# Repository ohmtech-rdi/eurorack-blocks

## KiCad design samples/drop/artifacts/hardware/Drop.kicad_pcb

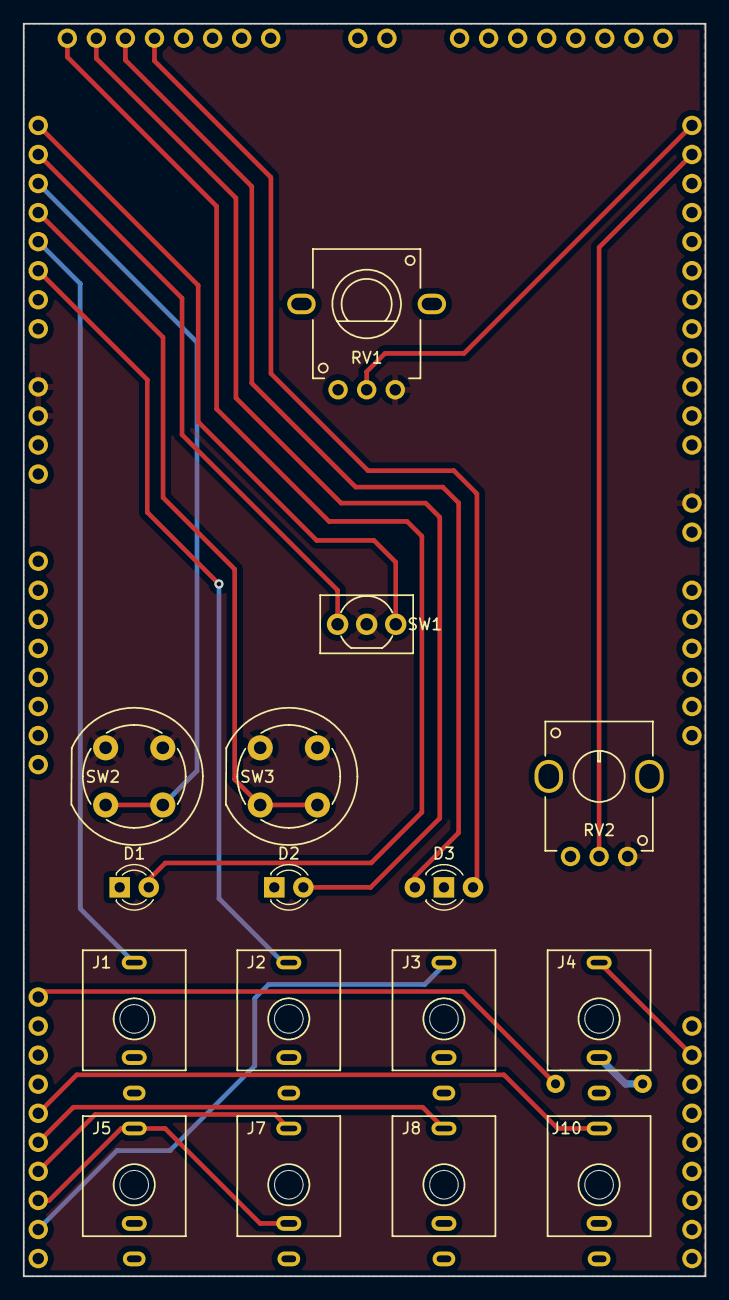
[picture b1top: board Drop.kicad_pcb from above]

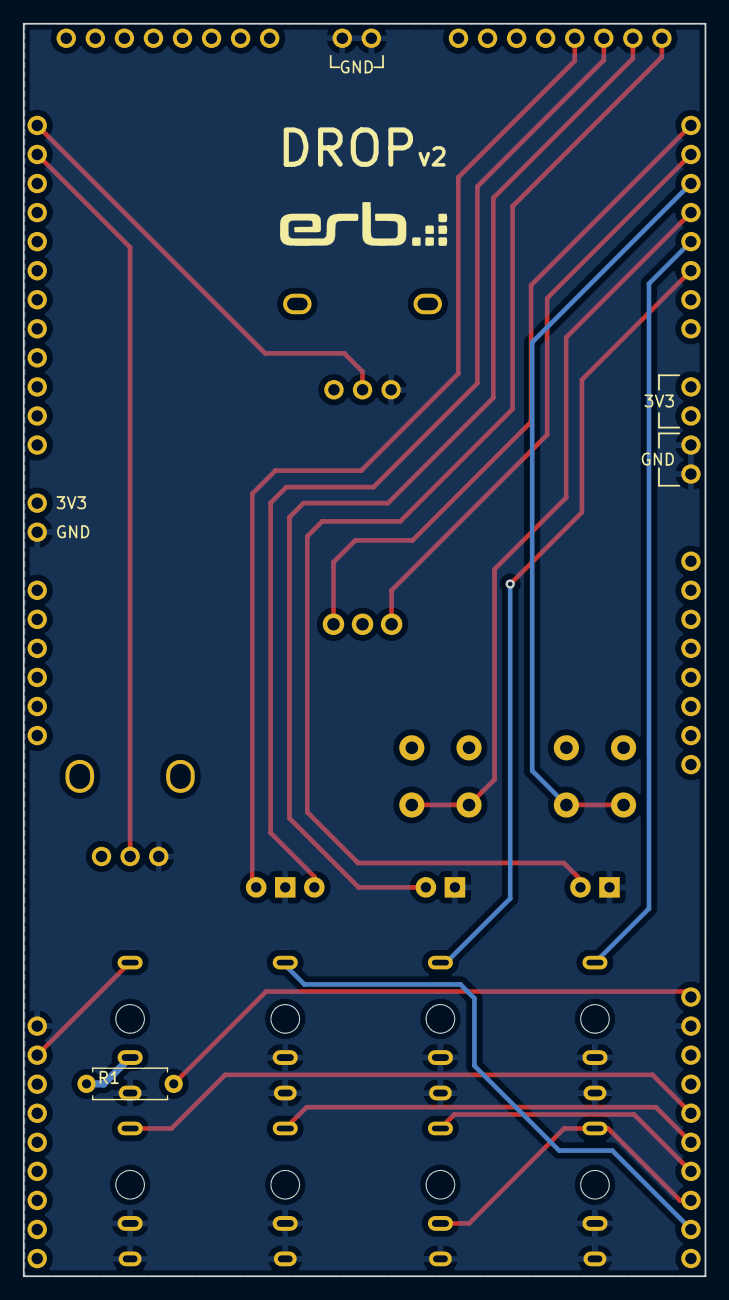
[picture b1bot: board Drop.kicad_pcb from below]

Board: 2 copper layers, 59.6 x 109.5 mm, 39 parts (12 on the bottom side), 22 nets.

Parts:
D1, D2: LED; LED_D3.0mm
D3: LED_Dual_ACA; LED_D3.0mm-3
H1: Header1; Empty
H2: Header2; Empty
H3: ROGAN 6PS; Empty
H4, H5, H6, H7, H8, H9, H10, H11: KNURLED NUT; Empty
J1, J2, J3, J4, J5, J7, J8, J10: IN; ThonkiconnJack
J6: POWER2; PinHeader_1x04_P2.54mm_Vertical
J9: POWER1; PinHeader_1x02_P2.54mm_Vertical
J11: GND; PinHeader_1x02_P2.54mm_Vertical
R1: 10k; R_Axial_DIN0207_L6.3mm_D2.5mm_P7.62mm_Horizontal
RV1: 100k; AlphaPot9ShaftD
RV2: 100k; SongHueiTallTrim9
SW1: SW_SPDT; SW_SPDT_Dailywell
SW2, SW3: SW_Push_Dual; SW_SPST_CKD6R
ZZ1: PX; PinHeader_1x12_P2.54mm_Vertical
ZZ2: CIX; PinHeader_1x09_P2.54mm_Vertical
ZZ3, ZZ7: BX; PinHeader_1x08_P2.54mm_Vertical
ZZ4, ZZ12: LX; PinHeader_1x08_P2.54mm_Vertical
ZZ5: ANALOG; PinHeader_1x10_P2.54mm_Vertical
ZZ10: SD; PinHeader_1x06_P2.54mm_Vertical

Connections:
+3V3: J6.1, J6.2, J9.1, RV1.3, RV2.3, SW1.2, SW2.1, SW3.1
AI1: J5.T, J7.TN, ZZ5.8
AI2: J7.T, ZZ5.7
AO1: J8.T, ZZ5.6
AO2: J10.T, ZZ5.5
B1: SW1.1, ZZ3.1
B2: SW1.3, ZZ3.2
B3: SW2.2, ZZ3.3
B4: SW3.2, ZZ3.4
B5: J1.T, ZZ3.5
B6: J2.T, ZZ3.6
CI1: J4.T, ZZ2.2
GND: D1.1, D2.1, D3.2, J1.S, J1.TN, J2.S, J2.TN, J3.S, J3.TN, J4.S, J5.S, J5.TN, J6.3, J6.4, J7.S, J8.S, J8.TN, J9.2, J10.S, J10.TN, J11.1, J11.2, RV1.1, RV2.1, ZZ2.1, ZZ5.2
GO1: J3.T, ZZ5.9
L1: D1.2, ZZ4.1
L2: D2.2, ZZ4.2
L3: D3.1, ZZ4.3
L4: D3.3, ZZ4.4
NPR0: R1.1, ZZ5.1
P1: RV1.2, ZZ1.1
P2: RV2.2, ZZ1.2
freq_cv-Net-(J1-PadTN): J4.TN, R1.2

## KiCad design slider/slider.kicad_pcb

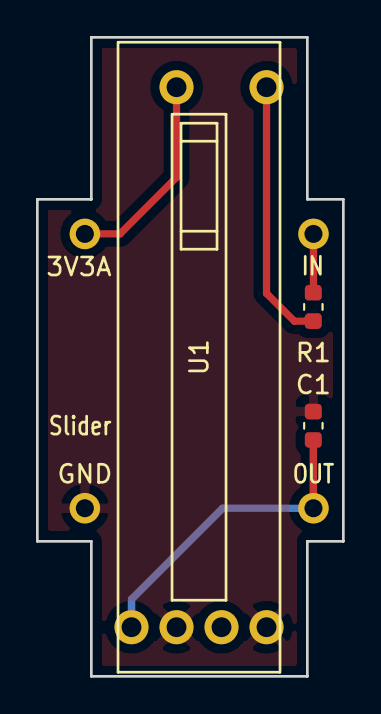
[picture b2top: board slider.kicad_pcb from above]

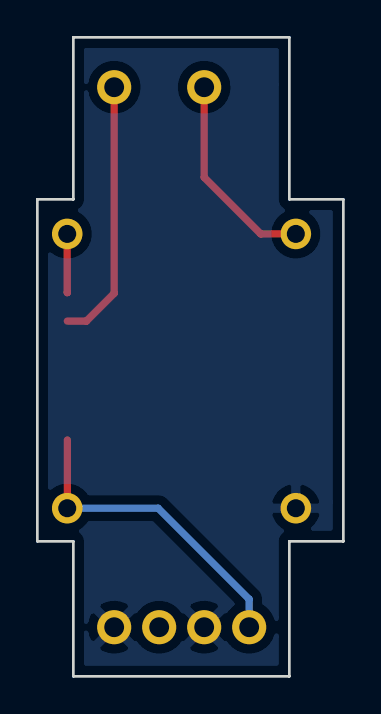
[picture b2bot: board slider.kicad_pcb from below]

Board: 2 copper layers, 17.0 x 35.5 mm, 7 parts (4 on the bottom side), 5 nets.

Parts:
C1: 100n; C_0603_1608Metric
J1, J2: OUT; PinHeader_1x01_P2.54mm_Vertical
J3, J4: GND; PinHeader_1x01_P2.54mm_Vertical
R1: 15k; R_0603_1608Metric
U1: PTL; PTL20

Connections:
+3V3: J3.1, U1.6
GND: C1.2, J4.1, U1.2, U1.4
IN: J2.1, R1.1
unnamed: R1.2, U1.5
OUT: C1.1, J1.1, U1.1

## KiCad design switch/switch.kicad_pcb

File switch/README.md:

# switch

## Description

This block is a simple switch. It can be used with 2 or 3 positions switches.

## Usage

This block provides a switch compatible with
[SPDT](https://en.wikipedia.org/wiki/Switch#Contact_terminology) On-On or On-Off-On.

It uses two GPIOs for each On state. In the case of the 3 position switch, the Off position
is detected when the two other GPIOs are low.

### Power

This module needs to be connected to the `3V3D` and `GND` lines from the power block.

> On Daisy Seed, use the 3V3 Digital Power on Pin 38, *not* the analog power. 

All `GND` pins are internally connected in the block.

### Signal

The signals `OUT0` and `OUT1` are the switch signal. It should be connected to any GPIO of the
target MCU, **preferably non-analog** GPIOs.

Those two pins will need to be **configured in pull-down mode** in software.

When using Daisy Seed as a development platform, see
[its pinout](https://images.squarespace-cdn.com/content/v1/58d03fdc1b10e3bf442567b8/1591827747342-HCXMM2NNR26SP5F4U2CJ/ke17ZwdGBToddI8pDm48kN5PbQBGNYbW-5Hm1pf8hRF7gQa3H78H3Y0txjaiv_0fDoOvxcdMmMKkDsyUqMSsMWxHk725yiiHCCLfrh8O1z4YTzHvnKhyp6Da-NYroOW3ZGjoBKy3azqku80C789l0kLp48N9LluBiCpBrPZntaz462IffsVrAff3VJkwKncM1HZuDnV98dfxM9yHlqFkUQ/DaisyPinoutRev4%404x.png?format=500w)
for details. The Daisy Seed has a total of 31 GPIOs, only 12 of which are analog.

## Design

> Gerber renders made with [tracespace view](https://tracespace.io/view/).

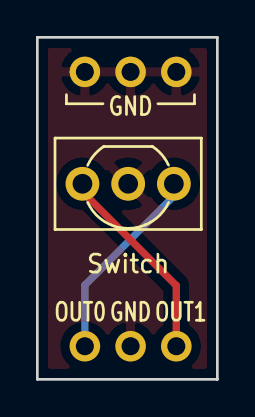
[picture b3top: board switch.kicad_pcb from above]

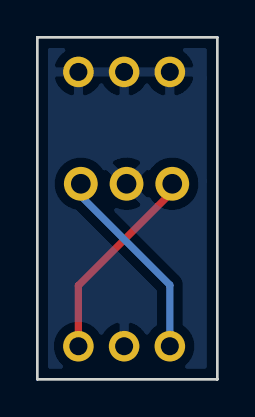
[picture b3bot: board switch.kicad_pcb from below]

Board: 2 copper layers, 10.0 x 19.0 mm, 3 parts (2 on the bottom side), 3 nets.

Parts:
J1: POWER; PinHeader_1x03_P2.54mm_Vertical
J2: OUT; PinHeader_1x03_P2.54mm_Vertical
SW1: SW_SPDT; SW_SPDT_Dailywell

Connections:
GND: J1.1, J1.2, J1.3, J2.2, SW1.2
OUT0: J2.1, SW1.3
OUT1: J2.3, SW1.1

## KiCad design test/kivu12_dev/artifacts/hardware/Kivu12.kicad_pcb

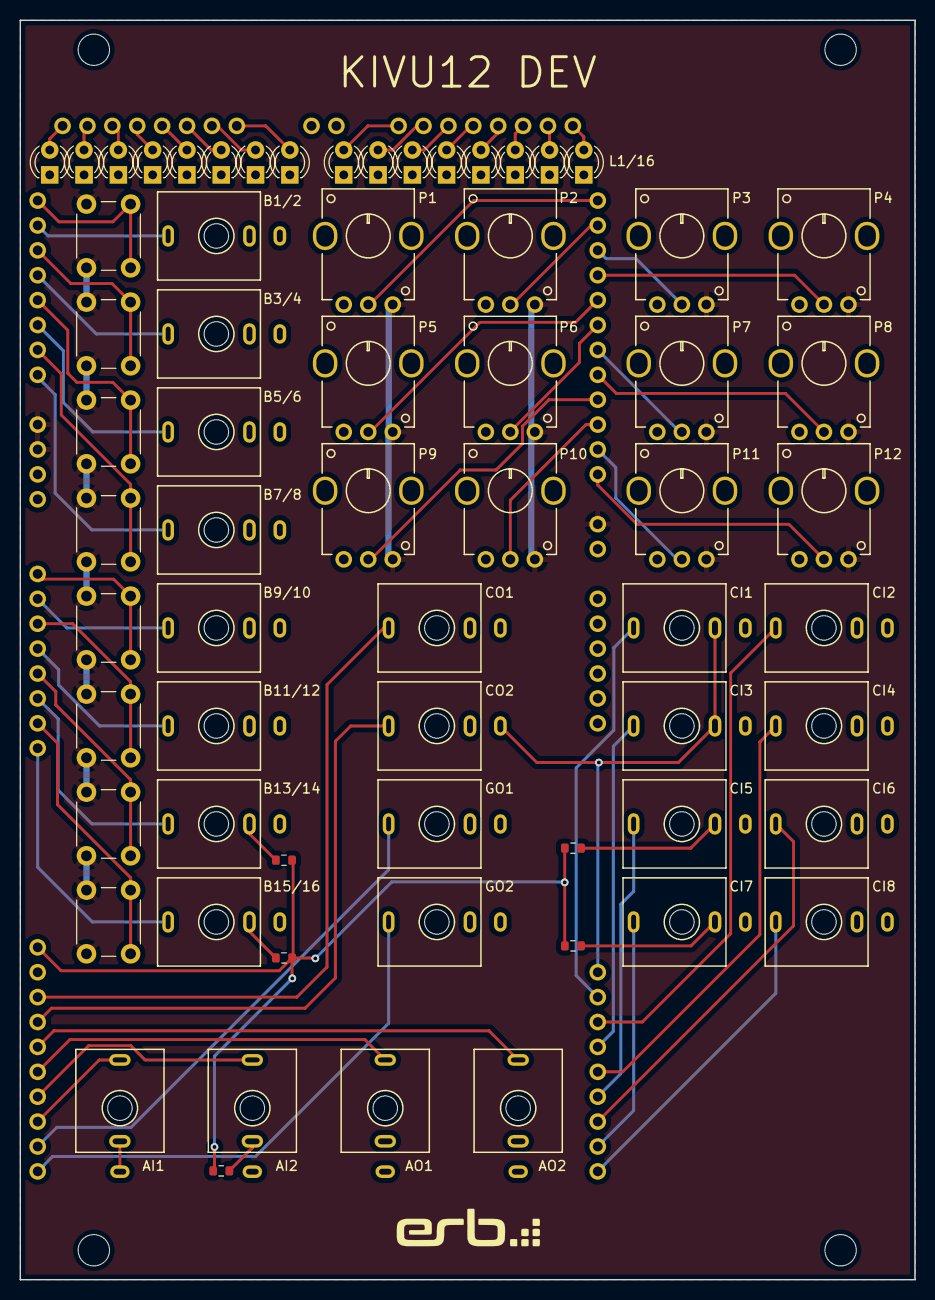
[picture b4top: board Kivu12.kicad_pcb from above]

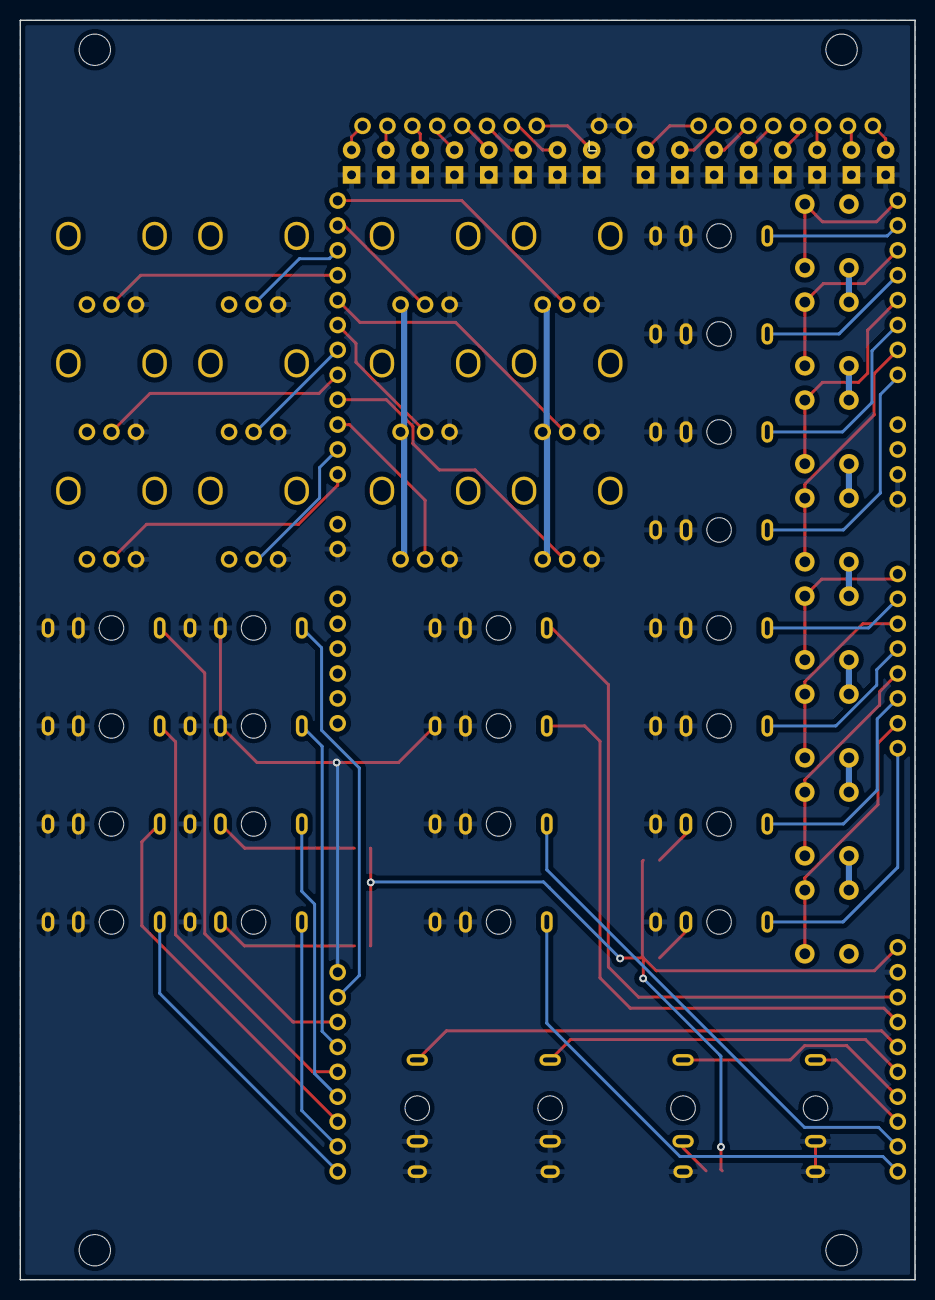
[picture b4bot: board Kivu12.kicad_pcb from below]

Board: 2 copper layers, 91.3 x 128.5 mm, 105 parts (11 on the bottom side), 62 nets.

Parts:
D1, D2, D3, D4, D5, D6, D7, D8, D9, D10, D11, D12, D13, D14, D15, D16: LED; LED_D3.0mm
H1: Header1; Empty
H2: Header2; Empty
H3, H5, H7, H9, H11, H13, H15, H17: CAP; Empty
H4, H6, H8, H10, H12, H14, H16, H18, H19, H20, H21, H22, H23, H24, H25, H26, H27, H28, H29, H30, H31, H32, H33, H34: KNURLED NUT; Empty
J1, J2, J3, J4, J5, J7, J8, J10, J12, J13, J14, J15, J16, J17, J18, J19, J20, J21, J22, J23, J24, J25, J26, J27: IN; ThonkiconnJack
J6: POWER2; PinHeader_1x04_P2.54mm_Vertical
J9: POWER1; PinHeader_1x02_P2.54mm_Vertical
J11: GND; PinHeader_1x02_P2.54mm_Vertical
RV1, RV2, RV3, RV4, RV5, RV6, RV7, RV8, RV9, RV10, RV11, RV12: 100k; SongHueiTallTrim9
SW1, SW2, SW3, SW4, SW5, SW6, SW7, SW8: SW_Push_Dual; SW_PUSH_6mm_H7.3mm
ZZ1: PX; PinHeader_1x12_P2.54mm_Vertical
ZZ2: CIX; PinHeader_1x09_P2.54mm_Vertical
ZZ3, ZZ7: BX; PinHeader_1x08_P2.54mm_Vertical
ZZ4, ZZ12: LX; PinHeader_1x08_P2.54mm_Vertical
ZZ5: ANALOG; PinHeader_1x10_P2.54mm_Vertical
ZZ10: SD; PinHeader_1x06_P2.54mm_Vertical

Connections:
+3V3: J6.1, J6.2, J9.1, RV1.3, RV2.3, RV3.3, RV4.3, RV5.3, RV6.3, RV7.3, RV8.3, RV9.3, RV10.3, RV11.3, RV12.3, SW1.1, SW2.1, SW3.1, SW4.1, SW5.1, SW6.1, SW7.1, SW8.1
AI1: J24.T, ZZ5.8
AI2: J25.T, ZZ5.7
AO1: J26.T, ZZ5.6
AO2: J27.T, ZZ5.5
B1: SW1.2, ZZ3.1
B2: J1.T, ZZ3.2
B3: SW2.2, ZZ3.3
B4: J2.T, ZZ3.4
B5: SW3.2, ZZ3.5
B6: J3.T, ZZ3.6
B7: SW4.2, ZZ3.7
B8: J4.T, ZZ3.8
B9: SW5.2, ZZ7.1
B10: J5.T, ZZ7.2
B11: SW6.2, ZZ7.3
B12: J7.T, ZZ7.4
B13: SW7.2, ZZ7.5
B14: J8.T, ZZ7.6
B15: SW8.2, ZZ7.7
B16: J10.T, ZZ7.8
CI1: J16.T, ZZ2.2
CI2: J17.T, ZZ2.3
CI3: J18.T, ZZ2.4
CI4: J19.T, ZZ2.5
CI5: J20.T, ZZ2.6
CI6: J21.T, ZZ2.7
CI7: J22.T, ZZ2.8
CI8: J23.T, ZZ2.9
CO1: J12.T, ZZ5.3
CO2: J13.T, ZZ5.4
GND: D1.1, D2.1, D3.1, D4.1, D5.1, D6.1, D7.1, D8.1, D9.1, D10.1, D11.1, D12.1, D13.1, D14.1, D15.1, D16.1, J1.S, J1.TN, J2.S, J2.TN, J3.S, J3.TN, J4.S, J4.TN, J5.S, J5.TN, J6.3, J6.4, J7.S, J7.TN, J8.S, J9.2, J10.S, J11.1, J11.2, J12.S, J12.TN, J13.S, J13.TN, J14.S, J14.TN, J15.S, J15.TN, J16.S, J16.TN, J17.S, J17.TN, J18.S, J18.TN, J19.S, J19.TN, J20.S, J21.S, J21.TN, J22.S, J23.S, J23.TN, J24.S, J24.TN, J25.S, J26.S, J26.TN, J27.S, J27.TN, RV1.1, RV2.1, RV3.1, RV4.1, RV5.1, RV6.1, RV7.1, RV8.1, RV9.1, RV10.1, RV11.1, RV12.1, ZZ2.1, ZZ5.2
GO1: J14.T, ZZ5.9
GO2: J15.T, ZZ5.10
L1: D1.2, ZZ4.1
L2: D2.2, ZZ4.2
L3: D3.2, ZZ4.3
L4: D4.2, ZZ4.4
L5: D5.2, ZZ4.5
L6: D6.2, ZZ4.6
L7: D7.2, ZZ4.7
L8: D8.2, ZZ4.8
L9: D9.2, ZZ12.1
L10: D10.2, ZZ12.2
L11: D11.2, ZZ12.3
L12: D12.2, ZZ12.4
L13: D13.2, ZZ12.5
L14: D14.2, ZZ12.6
L15: D15.2, ZZ12.7
L16: D16.2, ZZ12.8
P1: RV1.2, ZZ1.1
P2: RV2.2, ZZ1.2
P3: RV3.2, ZZ1.3
P4: RV4.2, ZZ1.4
P5: RV5.2, ZZ1.5
P6: RV6.2, ZZ1.6
P7: RV7.2, ZZ1.7
P8: RV8.2, ZZ1.8
P9: RV9.2, ZZ1.9
P10: RV10.2, ZZ1.10
P11: RV11.2, ZZ1.11
P12: RV12.2, ZZ1.12

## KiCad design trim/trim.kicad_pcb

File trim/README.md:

# trim

## Description

This block is a simple potentiometer, using a trim pot, typically used for attenuverters.
Its design is detailed [here](./documentation/design.md).

## Connecting

- This block needs its `GND` to be connected to the ground. All `GND` pins are connected
   internally,
- This block needs its `3V3A` to be connected to the Daisy Seed 3V3 Analog Power I/O on Pin 21,
- The signal `OUT` is the potentiometer value. It should be connected to any Analog GPIO of the
   target MCU. See [Daisy Seed pinout](https://images.squarespace-cdn.com/content/v1/58d03fdc1b10e3bf442567b8/1591827747342-HCXMM2NNR26SP5F4U2CJ/ke17ZwdGBToddI8pDm48kN5PbQBGNYbW-5Hm1pf8hRF7gQa3H78H3Y0txjaiv_0fDoOvxcdMmMKkDsyUqMSsMWxHk725yiiHCCLfrh8O1z4YTzHvnKhyp6Da-NYroOW3ZGjoBKy3azqku80C789l0kLp48N9LluBiCpBrPZntaz462IffsVrAff3VJkwKncM1HZuDnV98dfxM9yHlqFkUQ/DaisyPinoutRev4%404x.png?format=500w) for details.

## Using

```c++
int main ()
{
   using namespace erb;

   Module module;
   Trim trim (module, AdcPin6);  // 1.

   module.run ([&](){
      float trim_value = trim;   // 2.
   });
}
```

1. Attach the trim to the module and specify the same analog pin as the one used for connecting,
2. Retrieve the normalised (in the  `0.f` to `1.f` range) or bipolar (in the `-1.f` to `1.f` range)
   floating-point trim value.

The `Trim` type is an alias to the `Pot` class.
The `Pot` class reference is available [here](./../pot/documentation/reference.md).

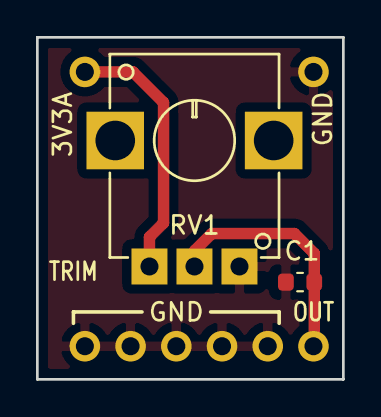
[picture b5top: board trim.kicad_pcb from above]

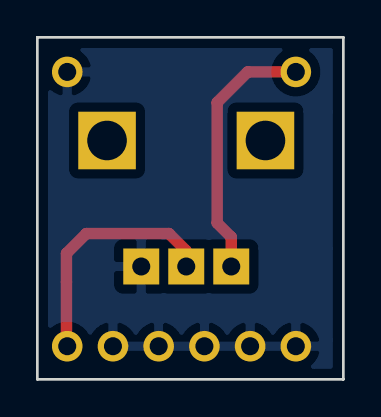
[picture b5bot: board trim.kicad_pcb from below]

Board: 2 copper layers, 17.0 x 19.0 mm, 5 parts (3 on the bottom side), 3 nets.

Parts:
C1: 100n; C_0603_1608Metric
J1: OUT; PinHeader_1x06_P2.54mm_Vertical
J2: GND; PinHeader_1x01_P2.54mm_Vertical
J3: 3V3; PinHeader_1x01_P2.54mm_Vertical
RV1: 100k; SongHueiTallTrim9

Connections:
+3V3: J3.1, RV1.1
GND: C1.1, J1.2, J1.3, J1.4, J1.5, J1.6, J2.1, RV1.3
OUT: C1.2, J1.1, RV1.2
